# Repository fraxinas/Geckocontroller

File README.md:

# Geckocontroller

(CC) 2021-2026 by Andreas Frisch <github@fraxinas.dev>

## OwO what's this?
**`geckocontroller` is an ESP32-based all-in-one solution for terrarium automation.**

|  |  |
| :------------------------------------------ | :----------------------------------------- |

There's an illustrated write-up of the project available at [purplegecko.de](https://purplegecko.de).

## Hardware Features
### Relay Output
* 3 mechanical DPST relays (TE Schrack RT444012), switching line and neutral
* individual load 8A each
* for Grow Light, Heat Lamp and Rain Pump

### Dimmer Output
* opto-coupler zero cross detection
* discrete triac phase-angle stage
* phase controller modulator
* fused mains entry

### RGB LED Output
* PWM driver
* for 12V RGB LED stripes

### White LED Output
* high-current PWM controller (gate driver + power MOSFET)
* screw terminals for an arbitrary constant voltage (e.g. 24V) white LED module

### FAN Output
* for an ATX type PC fan
* PWM and tachometer pins
* power cut-off circuitry for completely stopping all types of fans

### Dallas Thermometer Input
* 2 inputs for DS18B20 bus temperature sensors

### I²C Ports
* BME280 Thermo/Hygro/Baro sensor module (ceiling)
* SHT-3xD Thermo/Hygro sensor (ground)

### Load Cell Input
* NAU7802-based load cell amplifier/ADC on I²C
* for weighing / occupancy detection

### USB-C Port
* USB-to-serial programming port
* upright through-hole receptacle with CH343G bridge

### WiFi
* ESP32 wifi client

### SPI / Addon Connector
* for future extensions like a display or console

### Documentation
* [Circuit Calculations](hardware/calculations/README.md)

## Hardware Revisions

| Revision | Date    | Milestone                                              |
| :------- | :------ | :----------------------------------------------------- |
| v1.0     | 2021-02 | First prototype PCB                                     |
| v1.1     | 2021-03 | Bodged prototype, hardware issues fixed                 |
| v1.2     | 2021-04 | Second revision PCB, in service since 2021-05           |
| v2.0     | 2026-09 | Mains section rebuilt, white channel added              |

### What changed in HW Rev 2.0

| Function       | v1.2                                              | v2.0                                                                            |
| :------------- | :------------------------------------------------ | :------------------------------------------------------------------------------ |
| Relay outputs  | 3 solid state relays, 1A, zero-cross, line only   | 3 mechanical DPST relays, 8A, switching line **and** neutral, freewheeling diodes |
| Dimmer         | random cross solid state relay                    | discrete triac stage: BT138S-800E, FOD4208SD driver, 6N139 zero-cross, RC snubber |
| Mains entry    | unfused                                           | TR5 holder + 5A 250V T fuse, dedicated `mains` net class with 6.4 mm clearance    |
| White light    | —                                                 | high-current PWM channel (MCP1416 gate driver + AOD442)                          |
| Load cell ADC  | HX711                                             | NAU7802 (I²C)                                                                    |
| USB / serial   | SMD receptacle + CP2102                           | upright through-hole receptacle + CH343G                                          |
| Sensor ports   | mixed JST PH and WAGO terminals                   | JST PH / XH throughout, DS18B20 moved to JST PH 3-pin                            |
| Module         | ESP32-WROOM-32                                    | ESP32-WROOM-32E-N4                                                               |
| Board          | 114.3 x 96.5 mm                                   | 126.0 x 110.5 mm                                                                  |

## Software

### Using ESPHome.io
* simple YAML configuration for different sensor / actor modules
* Through Home Assistant web interface:
  * data logging and visualization of all environmental readings
  * manually control all actors, modify set points of controllers

### Weather Simulation
* use Nouvelle-Calédonie (Crested Gecko's natural habitat) real weather records
* use temperature, humidity, rain and sky cover values for creating a realistic varied simulation of the habitants' indigenous environment
* simulated sunrise, sunset, lightening storm

### Documentation
* [How-to Setup & Calibrate](software/README.md)

## Console unit
* ESP32-DevKitC with a 2.4" ILI9341 320x240 touch display (MSP2402), wired with dupont wires
  (wiring in [gecko-console.yaml](software/gecko-console.yaml))
* remote controls the main unit through home assistant via WiFi, operated by touch
* start page with a live animated sky following the simulated weather and sun
* pages for thermostat, hygrostat & rain, wind, lights with HSL color picker for scenic light, gecko nest & weight, light scene tests, settings
* Original dedicated console hardware platform with rotary encoder, MH-Z19 CO<sub>2</sub> sensor, piezo buzzer and RGB LEDs got a new life as an independent ESPHome air quality monitor

## TODO
### Controller unit
- [x] 3d-printed cases for BME280 sensor and console
- [x] rainfall/humidity automation
- [x] ventilation automation
- [x] moonlight simulation
- [x] thunderstorm simulation
- [x] climate failover + alarms
- [x] photos / documentation

## Project Diary
| Date       | Version | Milestone                                        |
| :--------- | :------ | :----------------------------------------------- |
| 2021-02-21 | v1.0    | Commission of 1st prototype PCB with aisler.net  |
| 2021-03-12 | v1.1    | First time programming of bodged prototype PCB   |
| 2021-04-10 |         | Fixed hardware issues with [LeoDJ](https://github.com/LeoDJ) & [Patagona](https://github.com/patagonaa) |
| 2021-04-15 | v1.2    | Commission of 2nd revision PCB with aisler.net   |
| 2021-05-03 | v1.2    | Completed PCB assembly, all modules working      |
| 2021-05-16 | v1.2    | Assembling of case and first deployment of unit  |
| 2022-01-02 |         | Added fogger to terrarium                        |
| 2022-01-09 |         | Base weather simulation on real historic records |
| 2022-01-28 | v1.0    | Order Console PCB at aisler.net & parts at LCSC  |
| 2022-02-18 |         | Assembled Console PCB                            |
| 2022-03-07 | v2.0    | New Hardware Revision of Console PCB             |
| 2026-09-21 | v2.0    | New Hardware Revision of Controller PCB          |
| 2026-10-17 |         | Deploy new Controller Hardware                   |
| 2026-11-18 |         | Replace HW of Console with ESP32-DevkitC         |
| 2026-11-26 |         | Featured project article on [Hackaday](https://hackaday.com/2026/11/26/location-accurate-weather-for-your-gecko/)             |

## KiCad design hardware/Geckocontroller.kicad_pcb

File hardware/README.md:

# Geckocontroller Hardware

## Calculations

### ACT4088 Feedback Resistors

with
* V<sub>out</sub> = 3.3V
* R<sub>FB1</sub> chosen 47k

* R<sub>FB2</sub> = R<sub>FB1</sub> / ((V<sub>out</sub> / 0.81) - 1) = 15289.156626506

Values are:
* `R103` = 47k
* `R101` = 15k
* `R102` = 287R

### HX711 Reference Voltage Resistors

with
* AVDD should be 100mV below VCC, so 3.20V
* AVDD = V<sub>BG</sub> * ( R1 + R2 ) / R2
* R1 chosen 47k

Values are:
* `R61` = 47k
* `R62` = 30k1

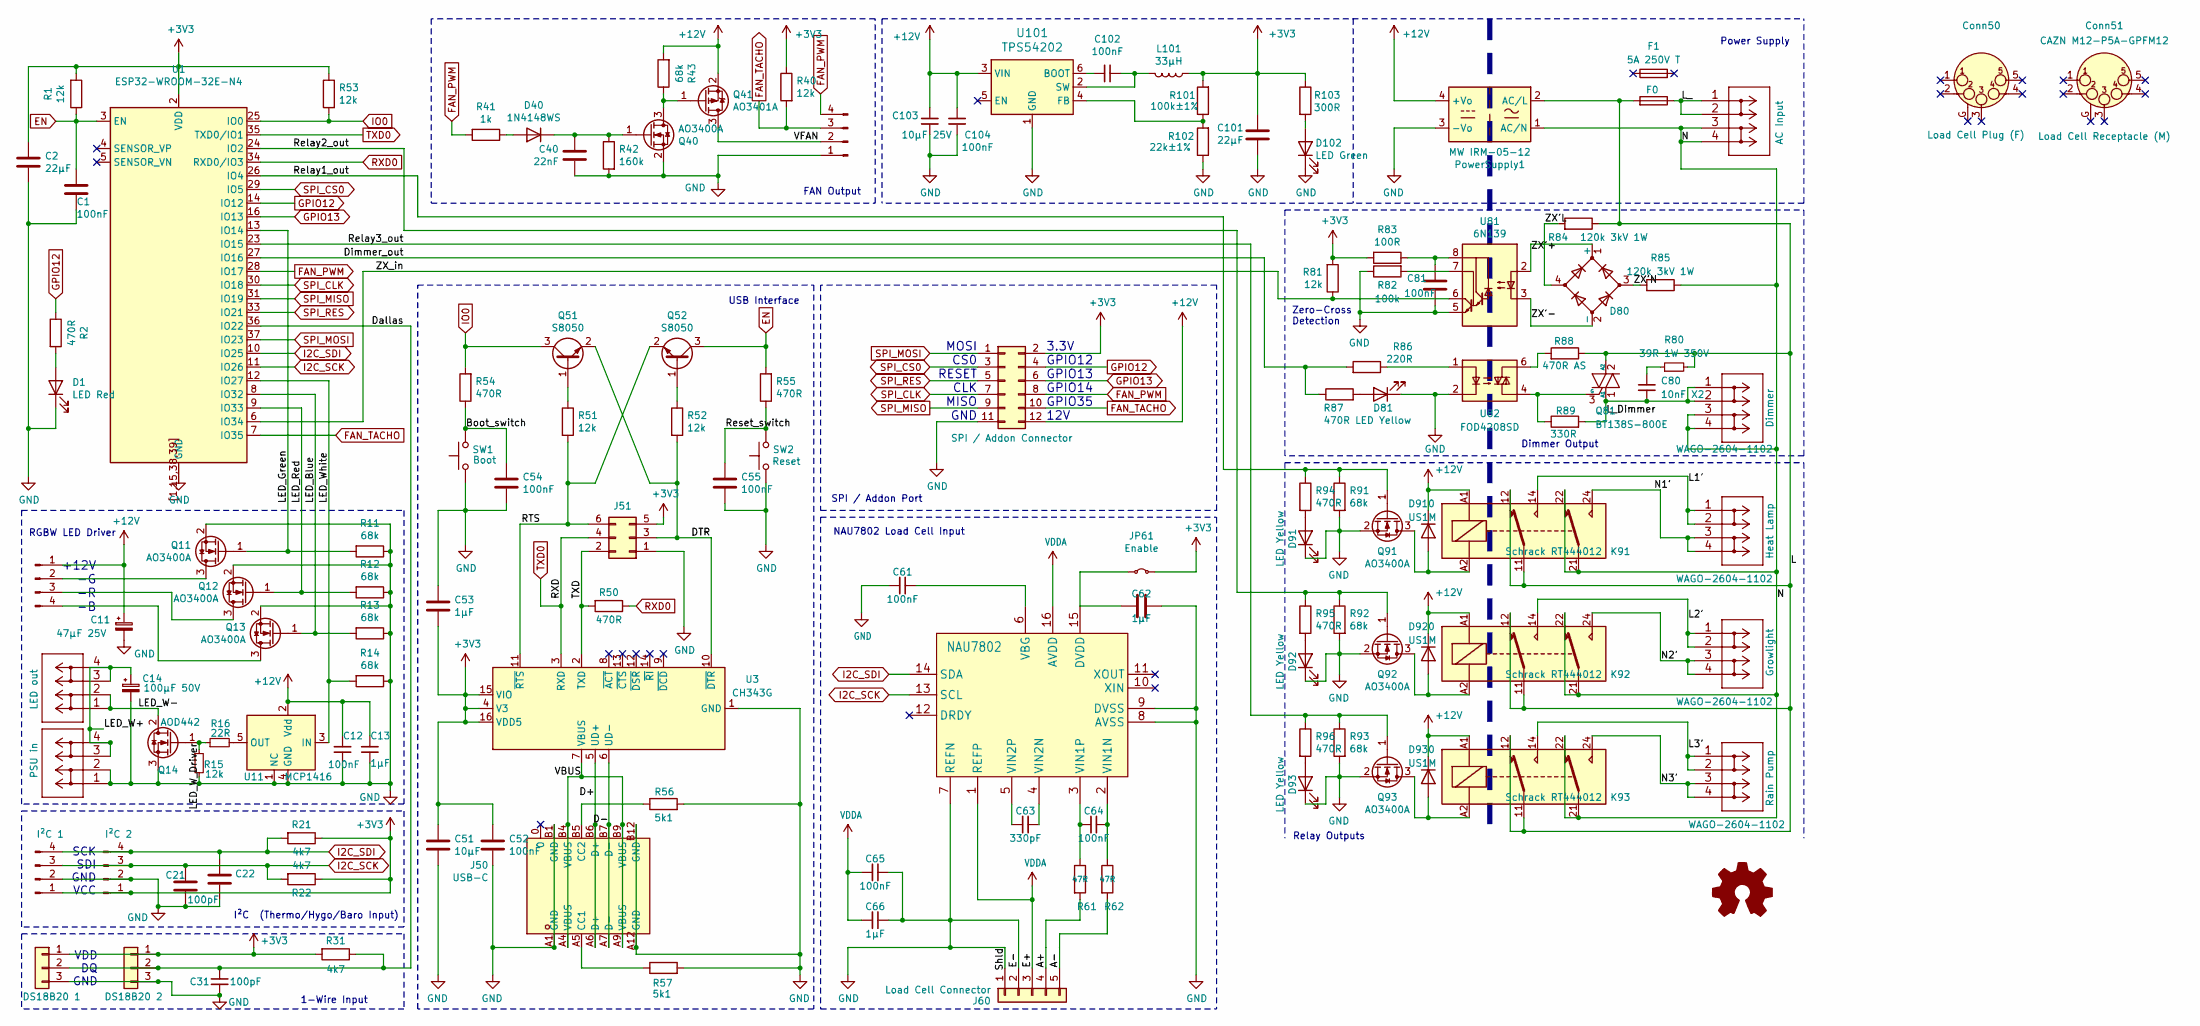
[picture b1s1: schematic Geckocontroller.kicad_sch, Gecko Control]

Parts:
C1, C12, C52, C54, C55, C61, C64, C65, C81, C102: 100nF; C_0603_1608Metric_Pad1.08x0.95mm_HandSolder; JLC Assembly true
C2: 22µF; C_1210_3225Metric_Pad1.33x2.70mm_HandSolder
C11: 47µF 25V; CP_Radial_D6.3mm_P2.50mm; LCSC Part C88791
C13, C62, C66: 1µF; C_0603_1608Metric_Pad1.08x0.95mm_HandSolder; JLC Assembly true
C14: 100µF 50V; CP_Radial_D8.0mm_P3.50mm; LCSC Part C109393
C21, C22, C31: 100pF; C_0603_1608Metric_Pad1.08x0.95mm_HandSolder; JLC Assembly true
C40: 22nF; C_0603_1608Metric_Pad1.08x0.95mm_HandSolder; JLC Assembly true
C51: 10µF; C_0805_2012Metric_Pad1.18x1.45mm_HandSolder
C53: 1µF; C_0805_2012Metric_Pad1.18x1.45mm_HandSolder; JLC Assembly true
C63: 330pF; C_0603_1608Metric_Pad1.08x0.95mm_HandSolder; JLC Assembly true
C80: 10nF X2; C_Rect_L13.0mm_W5.0mm_P10.00mm_FKS3_FKP3_MKS4; LCSC Part C489078
C101: 22µF; C_1210_3225Metric_Pad1.33x2.70mm_HandSolder; LCSC Part C12891
C103: 10µF 25V; C_0805_2012Metric_Pad1.18x1.45mm_HandSolder; LCSC Part C15850
C104: 100nF; C_0805_2012Metric_Pad1.18x1.45mm_HandSolder; JLC Assembly true
Conn50: CAZN M12-P5A-GPFM12
Conn51: CAZN M12-P5A-GPFM12; LCSC Part M12-P5A-GPFM12
D1: LED Red; LED_0805_2012Metric_Pad1.15x1.40mm_HandSolder; LCSC Part C84256
D40: 1N4148WS; D_SOD-323_HandSoldering; LCSC Part C2128
D80: MB10S; TO-269AA; LCSC Part C2488
D81, D91, D92, D93: LED Yellow; LED_0805_2012Metric_Pad1.15x1.40mm_HandSolder; LCSC Part C2296
D102: LED Green; LED_0805_2012Metric_Pad1.15x1.40mm_HandSolder; LCSC Part C2297
D910, D920, D930: US1M; D_SMA; LCSC Part C412437
F0: Fuseholder_TR5_Littelfuse_No560_No460; LCSC Part C142909
F1: 5A 250V T; Fuse_Littelfuse_372_D8.50mm; LCSC Part C142820
J11: JST_XH_B4B-XH-A; JST_XH_B4B-XH-A_1x04_P2.50mm_Vertical; LCSC Part C144395
J12, J13: WAGO-2601-3102
J21, J22: JST_PH_B4B-PH-K; JST_PH_B4B-PH-K_1x04_P2.00mm_Vertical; LCSC Part C131334
J31, J32: JST_PH_B3B-PH-K; JST_PH_B3B-PH-K_1x03_P2.00mm_Vertical; LCSC Part C131339
J40: Molex_KK-254_AE-6410-04A; Molex_KK-254_AE-6410-04A_1x04_P2.54mm_Vertical; LCSC Part C19795120
J50: USB-C; USB-C-TH_SHOUHAN_TYPE-C-14PLC-H10.0; MPN TYPE-C 14PLC-H10.0; LCSC Part C3151746
J51: UART; PinSocket_2x03_P2.54mm_Vertical; LCSC Part C22373908
J60: JST_XH_B5B-XH-A; JST_XH_B5B-XH-A_1x05_P2.50mm_Vertical; LCSC Part C157991
J70: IDC-Header_2x06; IDC-Header_2x06_P2.54mm_Vertical
J81, J91, J92, J93, J101: WAGO-2604-1102; WAGO-2604-1102-bare
JP61: Enable; PinHeader_1x02_P2.54mm_Vertical
K91, K92, K93: Schrack RT444012; Relay_DPDT_Schrack-RT2-FormC_RM5mm; LCSC Part C469133
L101: 33µH; L_TechFuse_SL0650; LCSC Part C149577
LOGO1: Logo_Open_Hardware_Small; OSHW-Logo2_14.6x12mm_Mask
PowerSupply1: MW IRM-05-12; Converter_ACDC_MeanWell_IRM-05-xx_THT; LCSC Part C6640067
Q11, Q12, Q13, Q40, Q91, Q92, Q93: AO3400A; SOT-23_Handsoldering; LCSC Part C20917
Q14: AOD442; TO-252-2; LCSC Part C87617
Q41: AO3401A; SOT-23_Handsoldering; LCSC Part C15127
Q51, Q52: S8050; SOT-23_Handsoldering; LCSC Part C2146
Q81: BT138S-800E; TO-252-2; LCSC Part C5380690
R1, R15, R40, R51, R52, R53, R81: 12k; R_0805_2012Metric_Pad1.20x1.40mm_HandSolder; JLC Assembly true
R2, R50, R54, R55, R87, R94, R95, R96: 470R; R_0805_2012Metric_Pad1.20x1.40mm_HandSolder; JLC Assembly true
R11, R12, R13, R14, R43, R91, R92, R93: 68k; R_0805_2012Metric_Pad1.20x1.40mm_HandSolder; JLC Assembly true
R16: 22R; R_0805_2012Metric_Pad1.20x1.40mm_HandSolder; JLC Assembly true
R21, R22, R31: 4k7; R_0805_2012Metric_Pad1.20x1.40mm_HandSolder; JLC Assembly true
R41: 1k; R_0805_2012Metric_Pad1.20x1.40mm_HandSolder; JLC Assembly true
R42: 160k; R_0805_2012Metric_Pad1.20x1.40mm_HandSolder
R56, R57: 5k1; R_0805_2012Metric_Pad1.20x1.40mm_HandSolder; JLC Assembly true
R61, R62: 47R; R_0805_2012Metric_Pad1.20x1.40mm_HandSolder; JLC Assembly true
R80: 39R 1W 350V; R_Axial_DIN0411_L9.9mm_D3.6mm_P12.70mm_Horizontal; LCSC Part C601812
R82: 100k; R_0805_2012Metric_Pad1.20x1.40mm_HandSolder; JLC Assembly true
R83: 100R; R_0805_2012Metric_Pad1.20x1.40mm_HandSolder; JLC Assembly true
R84, R85: 120k 3kV 1W; R_2512_6332Metric_Pad1.40x3.35mm_HandSolder; LCSC Part C2779433
R86: 220R; R_0805_2012Metric_Pad1.20x1.40mm_HandSolder; JLC Assembly true
R88: 470R AS; R_2512_6332Metric; LCSC Part C965926
R89: 330R; R_1206_3216Metric_Pad1.30x1.75mm_HandSolder
R101: 100k±1%; R_0603_1608Metric_Pad0.98x0.95mm_HandSolder; LCSC Part C25803
R102: 22k±1%; R_0603_1608Metric_Pad0.98x0.95mm_HandSolder; LCSC Part C31850
R103: 300R; R_0603_1608Metric_Pad0.98x0.95mm_HandSolder; LCSC Part C23025
SW1, SW2: Tactile Switch SPST 5mm 6mm x 6mm Through Hole; SW_PUSH_6mm; LCSC Part C393938
U1: ESP32-WROOM-32E-N4; ESP32-WROOM-32E; LCSC Part C701341
U3: CH343G; SOIC-16_3.9x9.9mm_P1.27mm; LCSC Part C2844153
U6: NAU7802; SOIC16_NARROW; LCSC Part C2614351
U11: MCP1416; SOT-23-5_HandSoldering; LCSC Part C83775
U81: 6N139; SMDIP-8_W9.53mm; LCSC Part C42186
U82: FOD4208SD; SMDIP-6_W9.53mm; LCSC Part C899305
U101: TPS54202; SOT-23-6_Handsoldering; LCSC Part C191884

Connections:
+3V3: C2.1, C51.1, C52.1, C53.2, C101.1, J21.1, J22.1, J31.1, J32.1, J51.5, J70.2, JP61.2 (B), L101.1, R1.2, R21.1, R22.1, R31.2, R40.1, R53.1, R81.2, R83.2, R101.2, R103.1, U1.2 (VDD), U3.4 (V3), U3.15 (VIO), U3.16 (VDD5)
+12V: C11.1, C12.2, C13.1, C103.1, C104.1, D910.1 (K), D920.1 (K), D930.1 (K), J11.1, J70.12, K91.A1, K92.A1, K93.A1, PowerSupply1.4 (+Vo), Q41.2 (S), R43.2, U11.2 (Vdd), U101.3 (VIN)
/A+: J60.4, R61.2
/A-: J60.5, R62.2
/Boot_switch: C54.1, R54.1, SW1.2
/D+: J50.A6 (D+), J50.B6 (D+), U3.5 (UD+)
/D-: J50.A7 (D-), J50.B7 (D-), U3.6 (UD-)
/DTR: J51.3, Q51.2 (E), R52.2, U3.10 (~DTR)
/Dallas: C31.2, J31.2, J32.2, R31.1, U1.36 (IO22)
/Dimmer_out: R86.2, R87.1, U1.27 (IO16)
/L: F0.2, K91.11, K91.12, K92.11, K92.12, K93.11, K93.12, PowerSupply1.2 (AC/L), Q81.2 (A2), R80.2, R84.1, R88.1
/L1': J91.1, J91.2, K91.14
/L2': J92.1, J92.2, K92.14
/L3': J93.1, J93.2, K93.14
/LED_Blue: Q13.1 (G), R13.2, U1.8 (IO32)
/LED_Green: Q11.1 (G), R11.2, U1.13 (IO14)
/LED_Red: Q12.1 (G), R12.2, U1.9 (IO33)
/LED_W+: C14.1, J12.3, J12.4, J13.3, J13.4
/LED_W-: J13.1, J13.2, Q14.2 (D)
/LED_W_Driver: Q14.1 (G), R15.1, R16.1
/LED_White: R14.2, U1.12 (IO27), U11.3 (IN)
/L_: F0.1, J101.1, J101.2
/L_Dimmer: C80.2, J81.1, J81.2, Q81.1 (A1), R89.2
/N: J81.3, J81.4, J101.3, J101.4, K91.21, K91.22, K92.21, K92.22, K93.21, K93.22, PowerSupply1.1 (AC/N), R85.1
/N1': J91.3, J91.4, K91.24
/N2': J92.3, J92.4, K92.24
/N3': J93.3, J93.4, K93.24
/RTS: J51.6, Q52.2 (E), R51.2, U3.11 (~RTS)
/Relay1_out: Q91.1 (G), R91.1, R94.1, U1.26 (IO4)
/Relay2_out: Q92.1 (G), R92.1, R95.1, U1.24 (IO2)
/Relay3_out: Q93.1 (G), R93.1, R96.1, U1.23 (IO15)
/Reset_switch: C55.1, R55.1, SW2.2
/TXD: J51.2, R50.2, U3.2 (TXD)
/VBUS: J50.A4 (VBUS), J50.A9 (VBUS), J50.B4 (VBUS), J50.B9 (VBUS), U3.7 (VBUS)
/VFAN: J40.2, Q41.3 (D)
/ZX'+: D80.1 (+), U81.2 (C1)
/ZX'-: D80.2 (-), U81.3 (C2)
/ZX'L: D80.4, R84.2
/ZX'N: D80.3, R85.2
/ZX_in: R81.1, U1.6 (IO34), U81.6 (VO2)
EN: C1.1, Q52.3 (C), R1.1, R55.2, U1.3 (EN)
FAN_PWM: J40.4, J70.8, R41.2, U1.28 (IO17)
FAN_TACHO: J40.3, J70.10, R40.2, U1.7 (IO35)
GND: C1.2, C2.2, C11.2, C12.1, C13.2, C14.2, C21.2, C22.2, C31.1, C40.1, C51.2, C52.2, C53.1, C54.2, C55.2, C61.1, C62.2, C65.1, C66.2, C81.2, C101.2, C103.2, C104.2, D1.1 (K), D81.1 (K), D91.1 (K), D92.1 (K), D93.1 (K), D102.1 (K), J12.1, J12.2, J21.2, J22.2, J31.3, J32.3, J40.1, J50.A1 (GND), J50.A12 (GND), J50.B1 (GND), J50.B12 (GND), J51.1, J60.1, J60.2, J70.11, PowerSupply1.3 (-Vo), Q11.2 (S), Q12.2 (S), Q13.2 (S), Q14.3 (S), Q40.2 (S), Q91.2 (S), Q92.2 (S), Q93.2 (S), R11.1, R12.1, R13.1, R14.1, R15.2, R42.2, R56.2, R57.2, R82.1, R91.2, R92.2, R93.2, R102.1, SW1.1, SW2.1, U1.1 (GND), U1.15 (GND), U1.38 (GND), U1.39 (GND), U1.[1,15,38,39] (GND), U3.1 (GND), U6.7 (REFN), U6.8 (AVSS), U6.9 (DVSS), U11.1 (NC), U11.4 (GND), U81.5 (GND), U82.2, U101.1 (GND)
GPIO12: J70.4, R2.1, U1.14 (IO12)
GPIO13: J70.6, U1.16 (IO13)
I2C_SCK: C21.1, J21.3, J22.3, R22.2, U1.11 (IO26), U6.13 (SCL)
I2C_SDI: C22.1, J21.4, J22.4, R21.2, U1.10 (IO25), U6.14 (SDA)
IO0: Q51.3 (C), R53.2, R54.2, U1.25 (IO0)
unnamed: C80.1, R80.1
unnamed: D1.2 (A), R2.2
unnamed: D40.2 (A), R41.1
unnamed: C40.2, D40.1 (K), Q40.1 (G), R42.1
unnamed: D81.2 (A), R87.2
unnamed: D91.2 (A), R94.2
unnamed: D92.2 (A), R95.2
unnamed: D93.2 (A), R96.2
unnamed: D102.2 (A), R103.2
unnamed: D910.2 (A), K91.A2, Q91.3 (D)
unnamed: D920.2 (A), K92.A2, Q92.3 (D)
unnamed: D930.2 (A), K93.A2, Q93.3 (D)
unnamed: J11.2, Q11.3 (D)
unnamed: J11.3, Q12.3 (D)
unnamed: J11.4, Q13.3 (D)
unnamed: J50.A5 (CC1), R57.1
unnamed: J50.B5 (CC2), R56.1
unnamed: C62.1, JP61.1 (A), U6.15 (DVDD)
unnamed: Q40.3 (D), Q41.1 (G), R43.1
unnamed: Q51.1 (B), R51.1
unnamed: Q52.1 (B), R52.1
unnamed: Q81.3 (G), R89.1, U82.4
unnamed: R86.1, U82.1
unnamed: R88.2, U82.6
unnamed: C61.2, U6.6 (VBG)
unnamed: C64.2, R62.1, U6.2 (VIN1N)
unnamed: C64.1, R61.1, U6.3 (VIN1P)
unnamed: C63.2, U6.4 (VIN2N)
unnamed: C63.1, U6.5 (VIN2P)
unnamed: R16.2, U11.5 (OUT)
unnamed: C81.1, R83.1, U81.8 (VCC)
unnamed: R82.2, U81.7 (VO1)
unnamed: C102.2, U101.6 (BOOT)
unnamed: R101.1, R102.2, U101.4 (FB)
unnamed: C102.1, L101.2, U101.2 (SW)
RXD0: R50.1, U1.34 (RXD0/IO3)
SPI_CLK: J70.7, U1.30 (IO18)
SPI_CS0: J70.3, U1.29 (IO5)
SPI_MISO: J70.9, U1.31 (IO19)
SPI_MOSI: J70.1, U1.37 (IO23)
SPI_RES: J70.5, U1.33 (IO21)
TXD0: J51.4, U1.35 (TXD0/IO1), U3.3 (RXD)
VDDA: C65.2, C66.1, J60.3, U6.1 (REFP), U6.16 (AVDD)

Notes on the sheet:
Relay Outputs
SCK SDI GND VCC
FAN Output
NAU7802 Load Cell Input
I²C (Thermo/Hygo/Baro Input)
MOSI CS0 RESET CLK MISO GND
VDD DQ GND
SPI / Addon Port
RGBW LED Driver
3.3V GPIO12 GPIO13 GPIO14 GPIO35 12V
1-Wire Input
Power Supply
Dimmer Output
Zero-Cross Detection
+12V -G -R -B
USB Interface

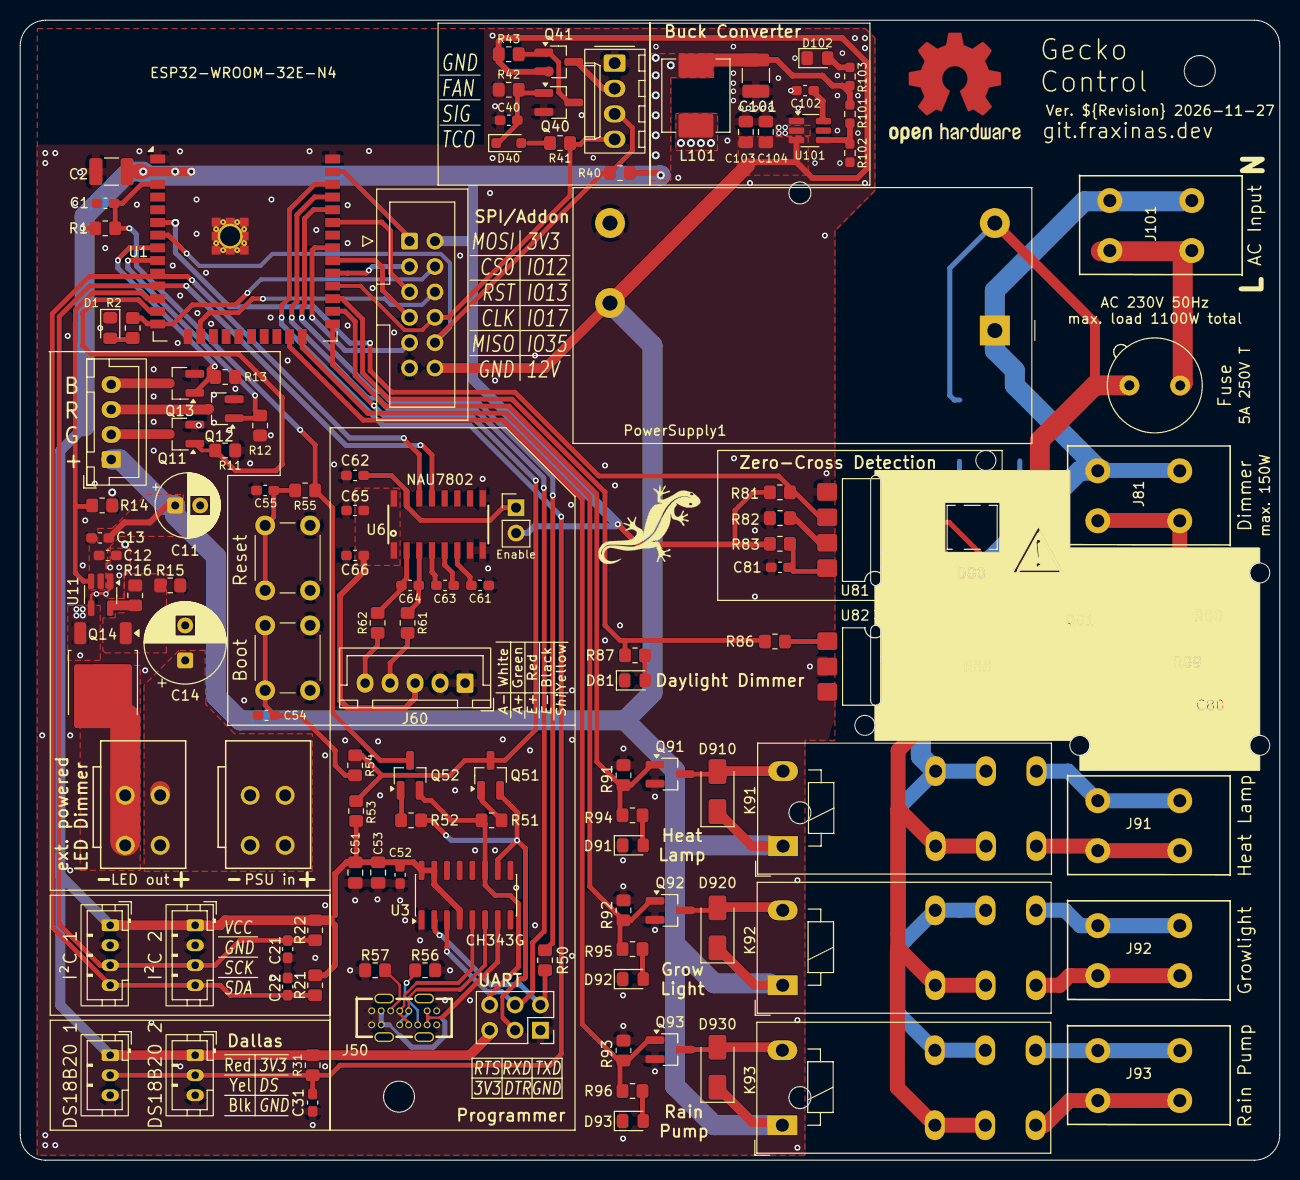
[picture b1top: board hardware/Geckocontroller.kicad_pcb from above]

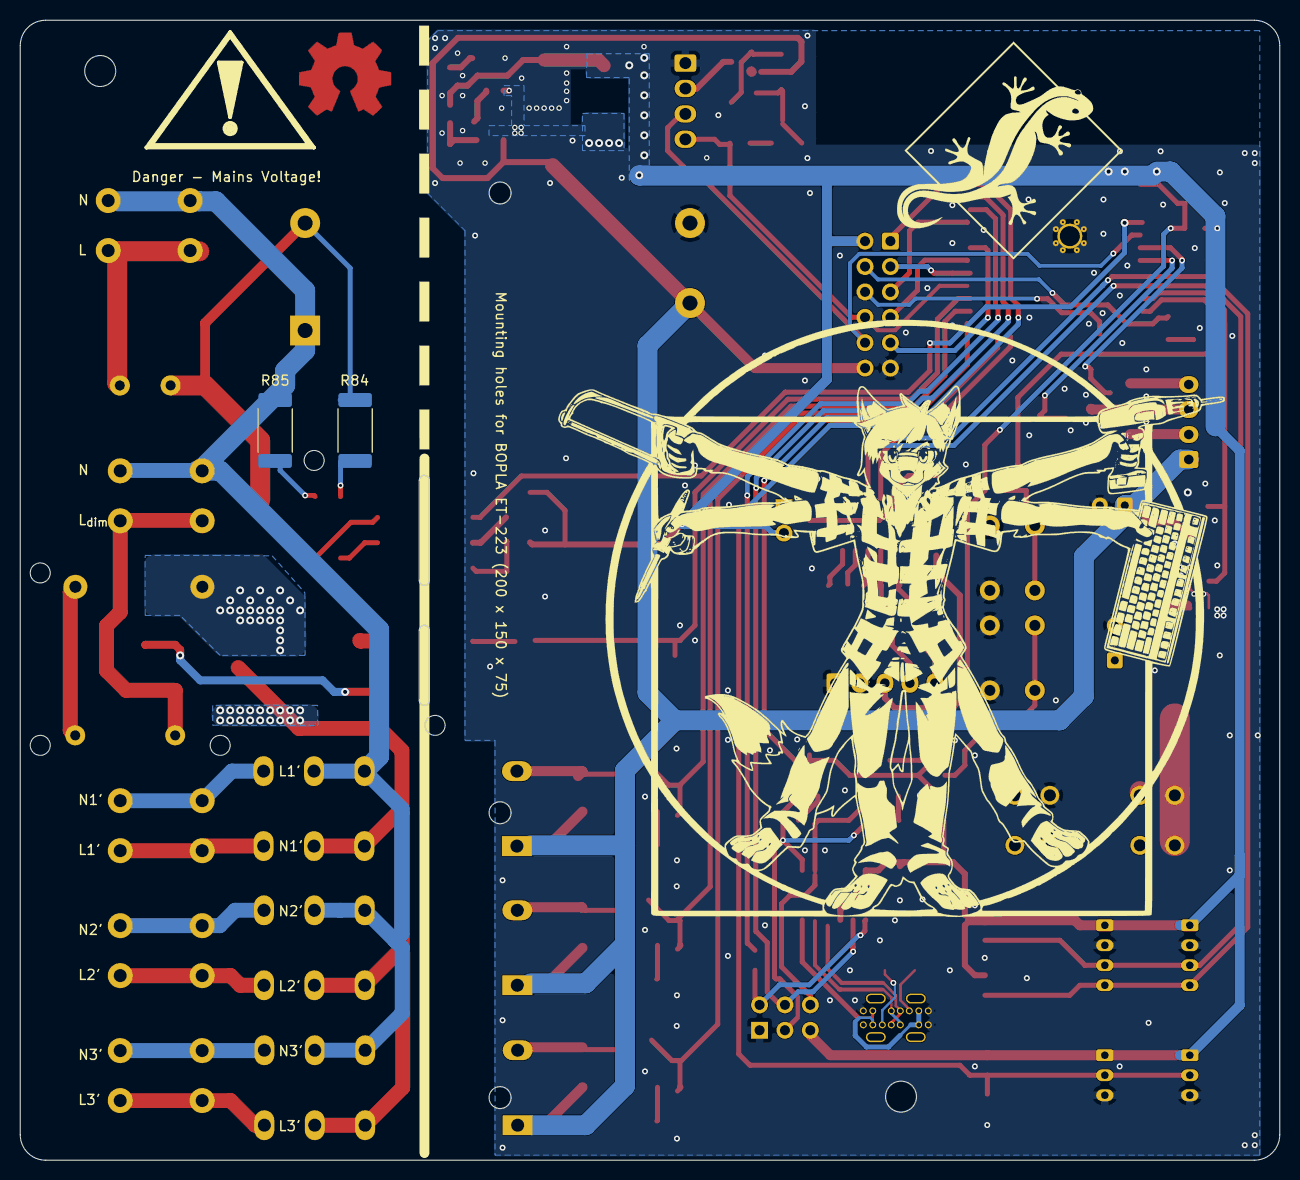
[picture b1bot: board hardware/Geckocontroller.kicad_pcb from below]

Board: 2 copper layers, 126.0 x 114.0 mm, 128 parts (2 on the bottom side), 92 nets.

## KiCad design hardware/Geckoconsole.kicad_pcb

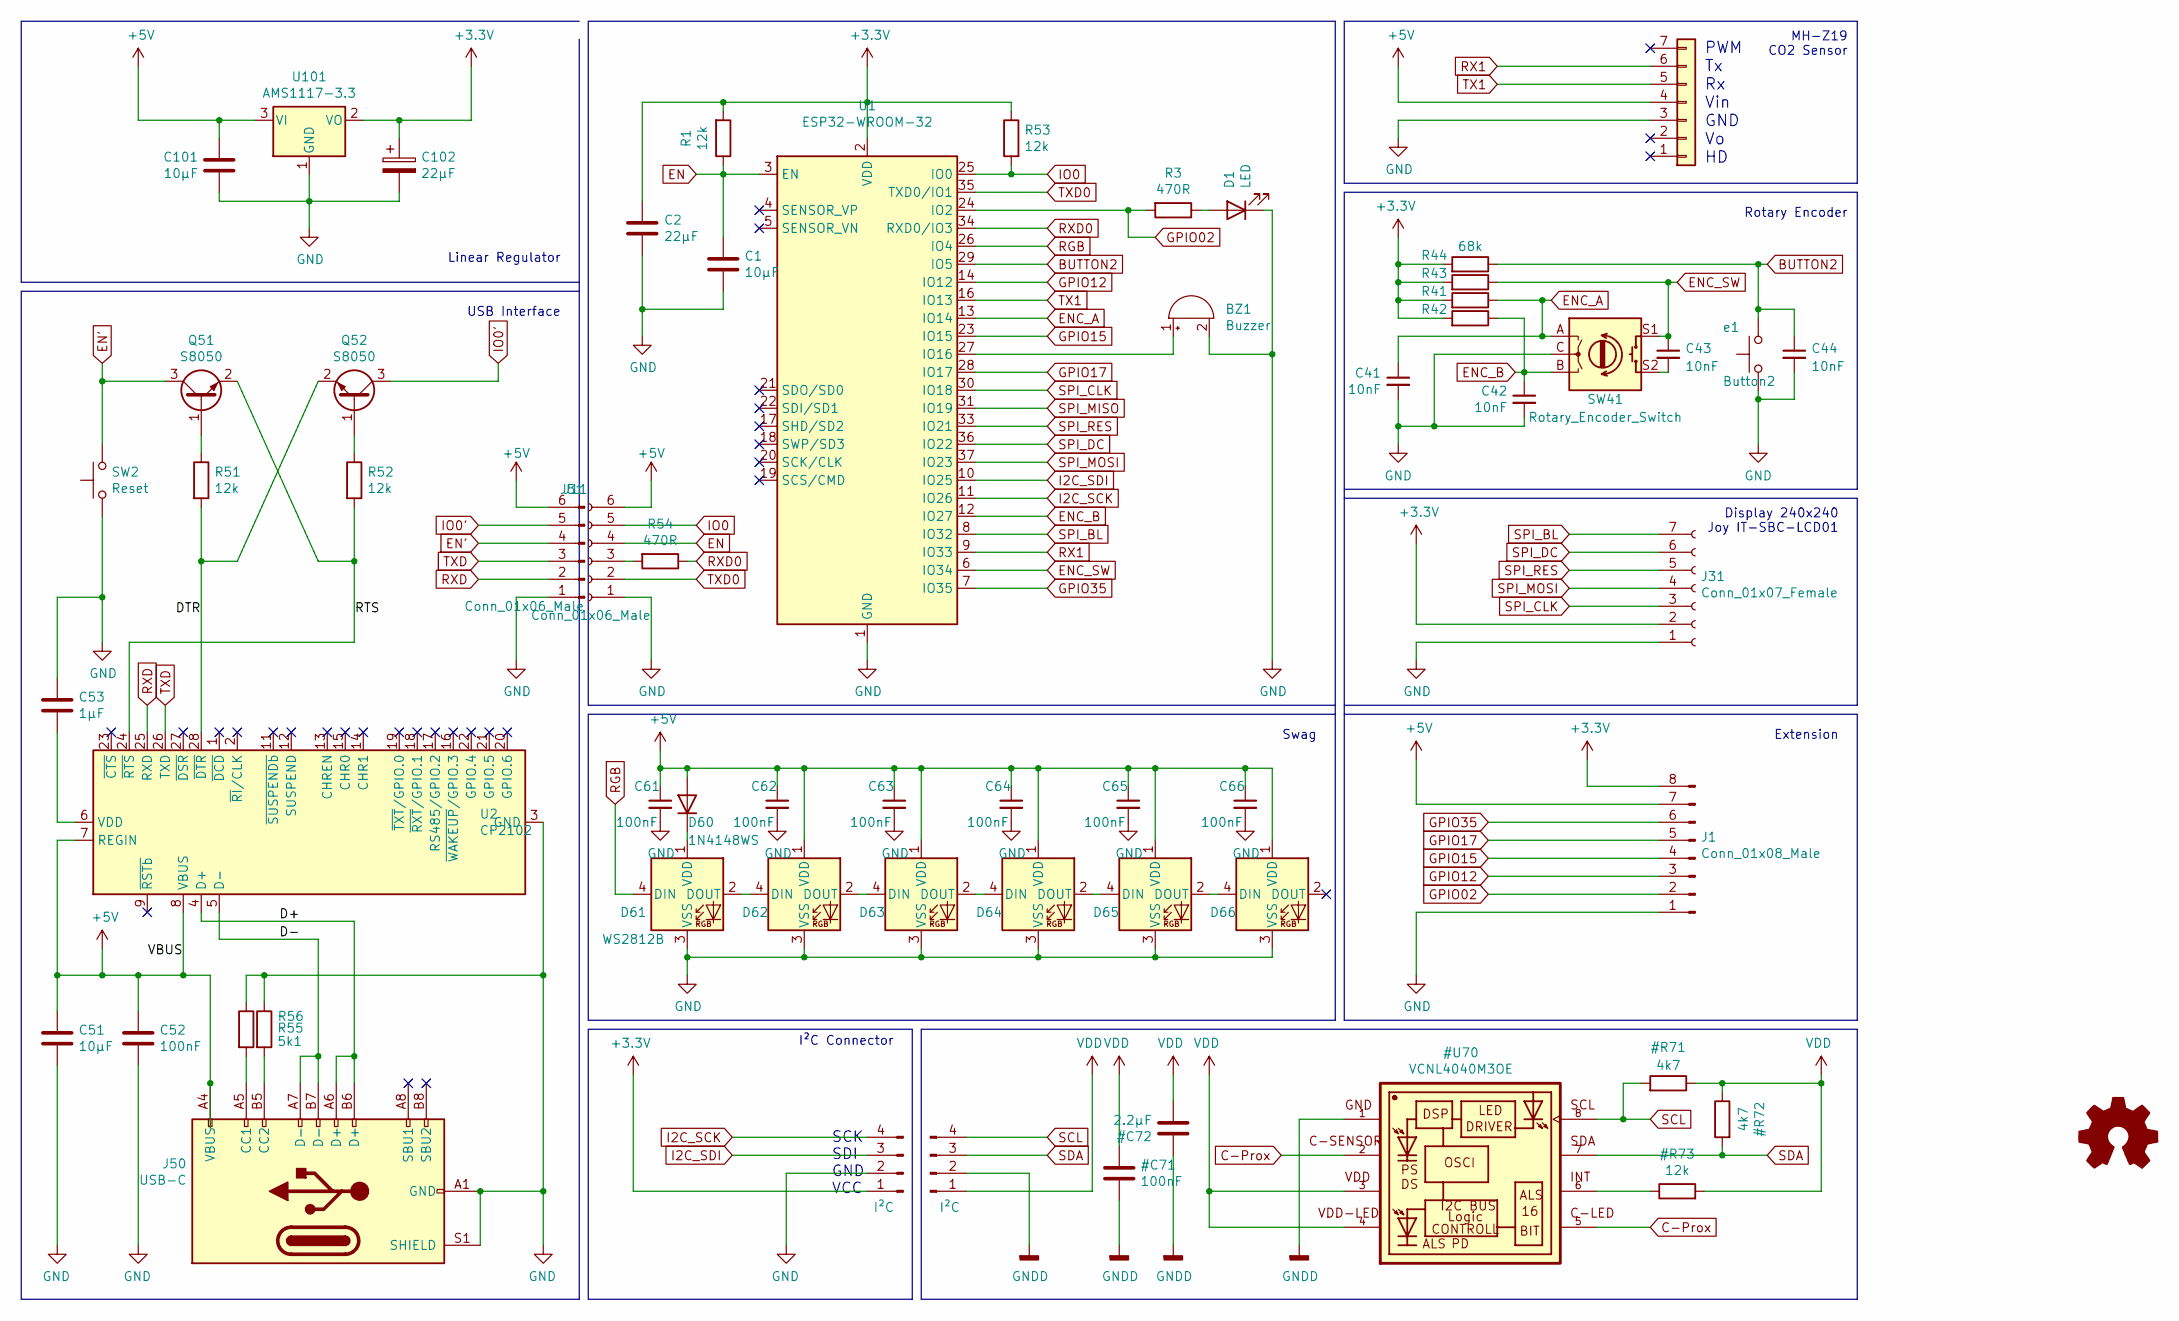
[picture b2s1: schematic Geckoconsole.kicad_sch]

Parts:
BZ1: Buzzer; Buzzer_Murata_PKMCS0909E4000-R1
C1, C51, C101: 10µF; C_0805_2012Metric_Pad1.18x1.45mm_HandSolder
C2: 22µF; C_1210_3225Metric_Pad1.33x2.70mm_HandSolder
C41, C42, C43, C44: 10nF; C_0603_1608Metric_Pad1.08x0.95mm_HandSolder
C52, C61, C62, C63, C64, C65, C66: 100nF; C_0603_1608Metric_Pad1.08x0.95mm_HandSolder
C53: 1µF; C_0603_1608Metric_Pad1.08x0.95mm_HandSolder
C102: 22µF; CP_Elec_4x5.3
D1: LED; LED_0805_2012Metric_Pad1.15x1.40mm_HandSolder
D60: 1N4148WS; D_SOD-323_HandSoldering
D61, D62, D63, D64, D65, D66: WS2812B; LED_WS2812B_PLCC4_5.0x5.0mm_P3.2mm
J1: Conn_01x08_Male; PinHeader_2x04_P2.54mm_Vertical
J11: Conn_01x06_Male; PinSocket_1x06_P2.00mm_Horizontal
J31: Conn_01x07_Female; PinSocket_1x07_P2.54mm_Vertical
J50: USB-C; USB_C_Receptacle_XKB_U262-16XN-4BVC11
J51: Conn_01x06_Male; PinHeader_1x06_P2.00mm_Horizontal
J70: I²C; PinSocket_1x04_P2.54mm_Vertical
J81: Conn_01x07; JST_PH_B7B-PH-K_1x07_P2.00mm_Vertical
LOGO1: Logo_Open_Hardware_Small; OSHW-Logo_5.7x6mm_Mask
Q51, Q52: S8050; SOT-23
R1, R51, R52, R53: 12k; R_0805_2012Metric_Pad1.20x1.40mm_HandSolder
R3, R54: 470R; R_0805_2012Metric_Pad1.20x1.40mm_HandSolder
R41, R42, R43, R44: 68k; R_0805_2012Metric_Pad1.20x1.40mm_HandSolder
R55, R56: 5k1; R_0805_2012Metric_Pad1.20x1.40mm_HandSolder
SW2: Reset; SW_SPST_B3U-1000P-B
SW41: Rotary_Encoder_Switch; Rotary_Encoder_Switched_PEC11R
U1: ESP32-WROOM-32
U2: CP2102; CP2102-QFN-28-modified
U101: AMS1117-3.3; SOT-223-3_TabPin2
e1: Button2; SW_PUSH_6mm_H5mm

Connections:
+3V3: C2.1, C102.1, J1.8, J31.2, J70.1, R1.2, R41.2, R42.2, R43.2, R44.2, R53.1, U1.2 (VDD), U101.2 (VO)
+5V: C51.1, C52.1, C61.1, C62.1, C63.1, C64.1, C65.1, C66.1, C101.1, D60.2 (A), D62.1 (VDD), D63.1 (VDD), D64.1 (VDD), D65.1 (VDD), D66.1 (VDD), J1.7, J11.6, J50.A4 (VBUS), J50.A9 (VBUS), J50.B4 (VBUS), J50.B9 (VBUS), J51.6, J81.4, U2.7 (REGIN), U2.8 (VBUS), U101.3 (VI)
/D+: J50.A6 (D+), J50.B6 (D+), U2.4 (D+)
/D-: J50.A7 (D-), J50.B7 (D-), U2.5 (D-)
/DTR: Q52.2 (E), R51.2, U2.28 (~DTR)
/RTS: Q51.2 (E), R52.2, U2.24 (~RTS)
BUTTON2: C44.1, R44.1, U1.29 (IO5), e1.2
EN: C1.1, J11.4, R1.1, U1.3 (EN)
EN': J51.4, Q51.3 (C), SW2.2
ENC_A: C41.1, R41.1, SW41.A, U1.13 (IO14)
ENC_B: C42.1, R42.1, SW41.B, U1.12 (IO27)
ENC_SW: C43.1, R43.1, SW41.S1, U1.6 (IO34)
GND: BZ1.2 (+), C1.2, C2.2, C41.2, C42.2, C44.2, C51.2, C52.2, C53.1, C61.2, C62.2, C63.2, C64.2, C65.2, C66.2, C101.2, C102.2, D1.1 (K), D61.3 (VSS), D62.3 (VSS), D63.3 (VSS), D64.3 (VSS), D65.3 (VSS), D66.3 (VSS), J1.1, J11.1, J31.1, J50.A1 (GND), J50.A12 (GND), J50.B1 (GND), J50.B12 (GND), J50.S1 (SHIELD), J51.1, J70.2, J81.3, R55.1, R56.1, SW2.1, SW41.C, U1.1 (GND), U1.15 (GND), U1.38 (GND), U1.39 (GND), U2.3 (GND), U2.29 (GND), U101.1 (GND), e1.1
GPIO02: J1.2, R3.2, U1.24 (IO2)
GPIO12: J1.3, U1.14 (IO12)
GPIO15: J1.4, U1.23 (IO15)
GPIO17: J1.5, U1.28 (IO17)
GPIO35: J1.6, U1.7 (IO35)
I2C_SCK: J70.4, U1.11 (IO26)
I2C_SDI: J70.3, U1.10 (IO25)
IO0: J11.5, R53.2, U1.25 (IO0)
IO0': J51.5, Q52.3 (C)
unnamed: BZ1.1 (-), U1.27 (IO16)
unnamed: C43.2, SW41.S2
unnamed: C53.2, U2.6 (VDD)
unnamed: D1.2 (A), R3.1
unnamed: D60.1 (K), D61.1 (VDD)
unnamed: D61.2 (DOUT), D62.4 (DIN)
unnamed: D62.2 (DOUT), D63.4 (DIN)
unnamed: D63.2 (DOUT), D64.4 (DIN)
unnamed: D64.2 (DOUT), D65.4 (DIN)
unnamed: D65.2 (DOUT), D66.4 (DIN)
unnamed: J11.3, R54.2
unnamed: J50.A5 (CC1), R56.2
unnamed: J50.B5 (CC2), R55.2
unnamed: Q51.1 (B), R51.1
unnamed: Q52.1 (B), R52.1
RGB: D61.4 (DIN), U1.26 (IO4)
RX1: J81.6, U1.9 (IO33)
RXD: J51.2, U2.25 (RXD)
RXD0: R54.1, U1.34 (RXD0/IO3)
SPI_BL: J31.7, U1.8 (IO32)
SPI_CLK: J31.3, U1.30 (IO18)
SPI_DC: J31.6, U1.36 (IO22)
SPI_MISO: U1.31 (IO19)
SPI_MOSI: J31.4, U1.37 (IO23)
SPI_RES: J31.5, U1.33 (IO21)
TX1: J81.5, U1.16 (IO13)
TXD: J51.3, U2.26 (TXD)
TXD0: J11.2, U1.35 (TXD0/IO1)

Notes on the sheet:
Display 240x240 Joy IT-SBC-LCD01
USB Interface
SCK SDI GND VCC
Linear Regulator
PWM Tx Rx Vin GND Vo HD
Rotary Encoder
I²C Connector
Swag
MH-Z19 CO2 Sensor
Extension

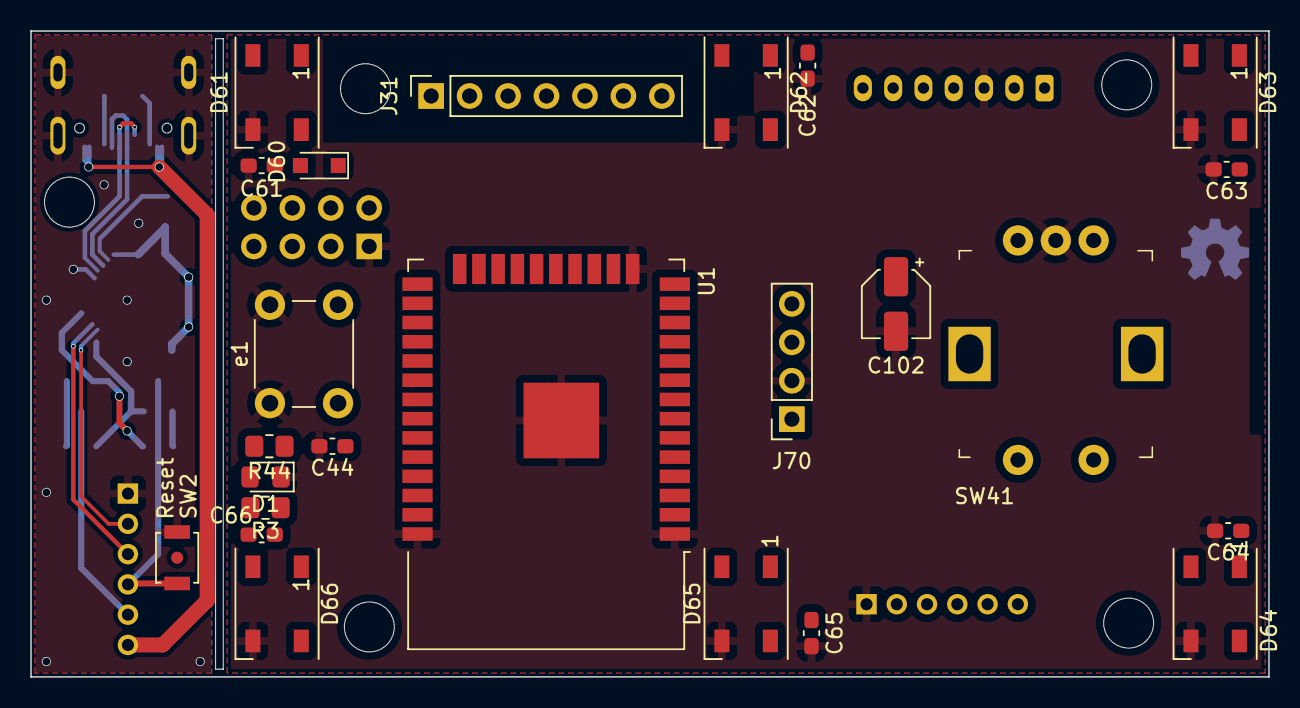
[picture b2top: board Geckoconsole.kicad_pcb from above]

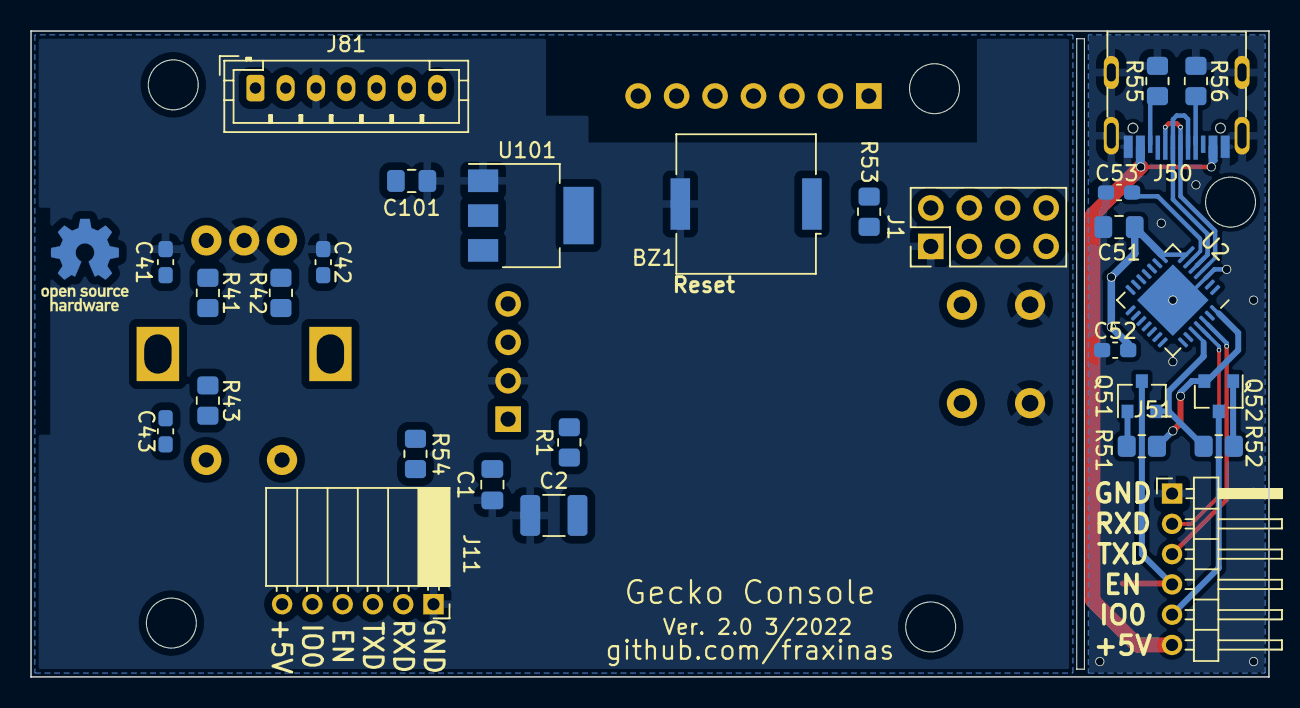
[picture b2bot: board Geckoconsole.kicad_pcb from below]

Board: 2 copper layers, 81.8 x 42.7 mm, 54 parts (30 on the bottom side), 49 nets.

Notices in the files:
parts and their libraries:
Copyright 2016 Accelerated Designs. All rights reserved.
